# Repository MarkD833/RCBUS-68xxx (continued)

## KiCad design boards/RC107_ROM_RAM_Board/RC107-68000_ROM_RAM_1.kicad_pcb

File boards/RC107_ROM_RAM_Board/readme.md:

# ROM & RAM board - V2 - 1M ROM + 1M RAM

# Details
The ROM & RAM board is designed to plug into an RCBus-80 backplane with support for 1M ROM (via 2x SST39SF040 FLASH chips) and 1M RAM (via 2x Alliance Memory AS6C4008 SRAMs). The FLASH chips and SRAMs are used as a pair to allow 16-bit wide memory accesses.

## Address Decoding
The address decoding is carried out by a 74LS138 and divides the lower 8Mb of memory space into eight 1Mb blocks. Each pair of chips can be assigned to any of the 8 chip selects - but not both pairs to the same chip select.

**Note:** If this is the only memory board in the 68000 system, then a pair of FLASH chips should be assigned to /CS0 so that the 68000 finds the stack pointer and program counter on boot.

**Note:** If this board is used with an MC68302 processor, then see the note further down regarding the ability to remap the ROM & RAM devices.

## Bus Width 
A 74LS139 generates the read and write signals for each of the memory chips and takes care of byte or word accesses.

## DTACK
A 74LS125 is used to generate a simple /DTACK signal driven directly from the EEPROM and SRAM chip select signals without any wait period.

# Board Assembly
Assembly of the board should be fairly straightforward as there are no surface mount devices to deal with.

Note the location of the decoupling capacitors for the memory devices are located within the IC sockets. THese decoupling capacitors should be bent over so that they do not interfere with the insertion of the memory chips.
 
When fitting the 80-pin right angle connector, initially only solder a couple of pins at opposite ends of the connector so that you can make any adjustments if the board is not vertical when fitted to the backplane.

Do not mix ROM & RAM chips in the same bank.

# Memory Bank Configuration
The pinout of the 32-pin FLASH and SRAM chips are slightly different and in order to accommodate both types, a pair of jumpers need to be set per chip. J6,J7,J8 & J9 set the memory type fitted to memory bank #0 and J2,J3,J4 & J5 set the memory type fitted to memory bank #1.

# Jumpers
+ FLASH ROM chips installed in Bank #1
  + J2: Jumper pins 1-2
  + J3: Jumper pins 2-3
  + J4: Jumper pins 1-2
  + J5: Jumper pins 2-3
+ RAM chips installed in Bank #1
  + J2: Jumper pins 2-3
  + J3: Jumper pins 1-2
  + J4: Jumper pins 2-3
  + J5: Jumper pins 1-2
+ FLASH ROM chips installed in Bank #0
  + J6: Jumper pins 2-3
  + J7: Jumper pins 1-2
  + J8: Jumper pins 2-3
  + J9: Jumper pins 1-2
+ RAM chips installed in Bank #0
  + J6: Jumper pins 1-2
  + J7: Jumper pins 2-3
  + J8: Jumper pins 1-2
  + J9: Jumper pins 2-3
+ J10: Memory Address selection
  + $000000 .. $0FFFFF
  + $100000 .. $1FFFFF
  + $200000 .. $2FFFFF
  + $300000 .. $3FFFFF
  + $400000 .. $4FFFFF
  + $500000 .. $5FFFFF
+ J11 (with J10): Specify the memory address for bank #0
+ J12 (with J10): Specify the memory address for bank #1
+ JP1: Solder link to connect RCBus /CS_ROM to /CS_BANK0 (Bank 0 must have FLASH memory fitted).
+ JP2: Solder link to connect RCBus /CS_RAM to /CS_BANK1 (Bank 1 must have SRAM memory fitted).

# MC68302 ROM & RAM Remapping

If the version of the MC68302 monitor is used that makes use of remapping the chip select signals, then the following hardware changes are required to this board:
  + U1 (74LS125) should be removed as the 68302 is configured to generate the /DTACK signals for /CS0 and /CS1 itself
  + U5 (74LS138) should be removed as the 68302 is configured to generate the chip select signals itself
  + Solder links JP1 and JP2 on the rear of the board must be made.
  
# Errors
Nothing yet - but give it time :-(

# History
+ v2.0 - corrected missing /CS signals, fixed J4 & J5 pitch, added 10K pullups to /CS lines
+ v1.0 - initial designed

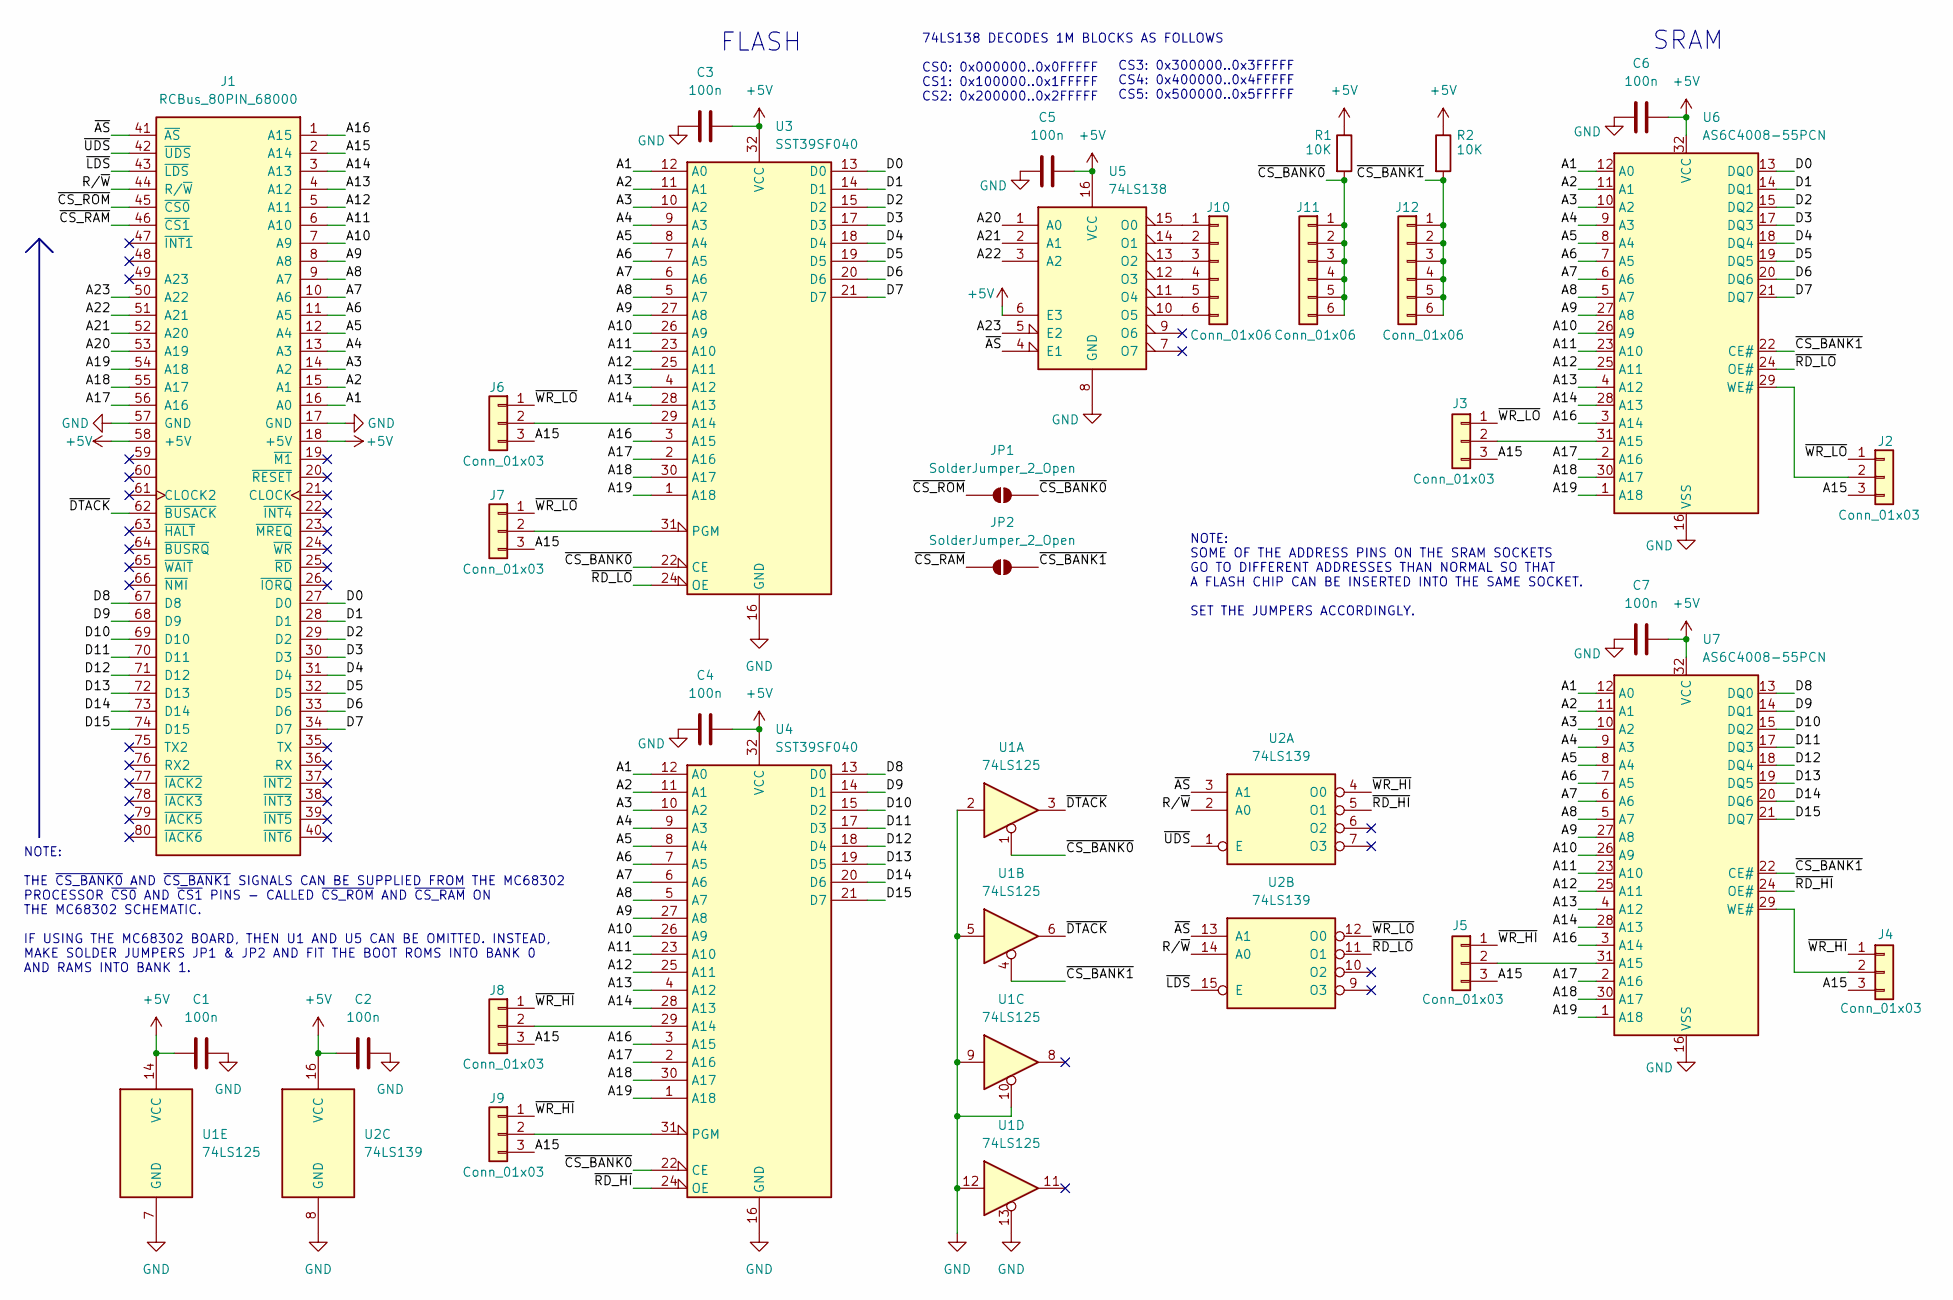
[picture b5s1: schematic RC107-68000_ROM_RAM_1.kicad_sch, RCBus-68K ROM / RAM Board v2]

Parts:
C1, C2, C3, C4, C5, C6, C7: 100n; C_Disc_D5.0mm_W2.5mm_P2.50mm
J1: RCBus_80PIN_68000; RCBus_80p_Medium
J2, J3, J4, J5, J6, J7, J8, J9: Conn_01x03; PinHeader_1x03_P2.54mm_Vertical
J10, J11, J12: Conn_01x06; PinHeader_1x06_P2.54mm_Vertical
JP1, JP2: SolderJumper_2_Open; SolderJumper-2_P1.3mm_Open_Pad1.0x1.5mm
R1, R2: 10K; R_Axial_DIN0207_L6.3mm_D2.5mm_P7.62mm_Horizontal
U1: 74LS125; DIP-14_W7.62mm
U2: 74LS139; DIP-16_W7.62mm
U3, U4: SST39SF040; DIP-32_W15.24mm
U5: 74LS138; DIP-16_W7.62mm
U6, U7: AS6C4008-55PCN; DIP-32_W15.24mm

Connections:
+5V: C1.1, C2.1, C3.2, C4.2, C5.2, C6.2, C7.2, J1.18 (+5V), J1.58 (+5V), R1.1, R2.1, U1.14 (VCC), U2.16 (VCC), U3.32 (VCC), U4.32 (VCC), U5.6 (E3), U5.16 (VCC), U6.32 (VCC), U7.32 (VCC)
/A1: J1.16 (A0), U3.12 (A0), U4.12 (A0), U6.12 (A0), U7.12 (A0)
/A2: J1.15 (A1), U3.11 (A1), U4.11 (A1), U6.11 (A1), U7.11 (A1)
/A3: J1.14 (A2), U3.10 (A2), U4.10 (A2), U6.10 (A2), U7.10 (A2)
/A4: J1.13 (A3), U3.9 (A3), U4.9 (A3), U6.9 (A3), U7.9 (A3)
/A5: J1.12 (A4), U3.8 (A4), U4.8 (A4), U6.8 (A4), U7.8 (A4)
/A6: J1.11 (A5), U3.7 (A5), U4.7 (A5), U6.7 (A5), U7.7 (A5)
/A7: J1.10 (A6), U3.6 (A6), U4.6 (A6), U6.6 (A6), U7.6 (A6)
/A8: J1.9 (A7), U3.5 (A7), U4.5 (A7), U6.5 (A7), U7.5 (A7)
/A9: J1.8 (A8), U3.27 (A8), U4.27 (A8), U6.27 (A8), U7.27 (A8)
/A10: J1.7 (A9), U3.26 (A9), U4.26 (A9), U6.26 (A9), U7.26 (A9)
/A11: J1.6 (A10), U3.23 (A10), U4.23 (A10), U6.23 (A10), U7.23 (A10)
/A12: J1.5 (A11), U3.25 (A11), U4.25 (A11), U6.25 (A11), U7.25 (A11)
/A13: J1.4 (A12), U3.4 (A12), U4.4 (A12), U6.4 (A12), U7.4 (A12)
/A14: J1.3 (A13), U3.28 (A13), U4.28 (A13), U6.28 (A13), U7.28 (A13)
/A15: J1.2 (A14), J2.3, J3.3, J4.3, J5.3, J6.3, J7.3, J8.3, J9.3
/A16: J1.1 (A15), U3.3 (A15), U4.3 (A15), U6.3 (A14), U7.3 (A14)
/A17: J1.56 (A16), U3.2 (A16), U4.2 (A16), U6.2 (A16), U7.2 (A16)
/A18: J1.55 (A17), U3.30 (A17), U4.30 (A17), U6.30 (A17), U7.30 (A17)
/A19: J1.54 (A18), U3.1 (A18), U4.1 (A18), U6.1 (A18), U7.1 (A18)
/A20: J1.53 (A19), U5.1 (A0)
/A21: J1.52 (A20), U5.2 (A1)
/A22: J1.51 (A21), U5.3 (A2)
/A23: J1.50 (A22), U5.5 (E2)
/D0: J1.27 (D0), U3.13 (D0), U6.13 (DQ0)
/D1: J1.28 (D1), U3.14 (D1), U6.14 (DQ1)
/D2: J1.29 (D2), U3.15 (D2), U6.15 (DQ2)
/D3: J1.30 (D3), U3.17 (D3), U6.17 (DQ3)
/D4: J1.31 (D4), U3.18 (D4), U6.18 (DQ4)
/D5: J1.32 (D5), U3.19 (D5), U6.19 (DQ5)
/D6: J1.33 (D6), U3.20 (D6), U6.20 (DQ6)
/D7: J1.34 (D7), U3.21 (D7), U6.21 (DQ7)
/D8: J1.67 (D8), U4.13 (D0), U7.13 (DQ0)
/D9: J1.68 (D9), U4.14 (D1), U7.14 (DQ1)
/D10: J1.69 (D10), U4.15 (D2), U7.15 (DQ2)
/D11: J1.70 (D11), U4.17 (D3), U7.17 (DQ3)
/D12: J1.71 (D12), U4.18 (D4), U7.18 (DQ4)
/D13: J1.72 (D13), U4.19 (D5), U7.19 (DQ5)
/D14: J1.73 (D14), U4.20 (D6), U7.20 (DQ6)
/D15: J1.74 (D15), U4.21 (D7), U7.21 (DQ7)
/R/~W: J1.44 (R/~W), U2.2 (A0), U2.14 (A0)
/~AS: J1.41 (~AS), U2.3 (A1), U2.13 (A1), U5.4 (E1)
/~CS_BANK0: J11.1, J11.2, J11.3, J11.4, J11.5, J11.6, JP1.2 (B), R1.2, U1.1, U3.22 (CE), U4.22 (CE)
/~CS_BANK1: J12.1, J12.2, J12.3, J12.4, J12.5, J12.6, JP2.2 (B), R2.2, U1.4, U6.22 (CE#), U7.22 (CE#)
/~CS_RAM: J1.46 (~CS1), JP2.1 (A)
/~CS_ROM: J1.45 (~CS0), JP1.1 (A)
/~DTACK: J1.62 (~BUSACK), U1.3, U1.6
/~LDS: J1.43 (~LDS), U2.15 (E)
/~RD_HI: U2.5 (O1), U4.24 (OE), U7.24 (OE#)
/~RD_LO: U2.11 (O1), U3.24 (OE), U6.24 (OE#)
/~UDS: J1.42 (~UDS), U2.1 (E)
/~WR_HI: J4.1, J5.1, J8.1, J9.1, U2.4 (O0)
/~WR_LO: J2.1, J3.1, J6.1, J7.1, U2.12 (O0)
GND: C1.2, C2.2, C3.1, C4.1, C5.1, C6.1, C7.1, J1.17 (GND), J1.57 (GND), U1.2, U1.5, U1.7 (GND), U1.9, U1.10, U1.12, U1.13, U2.8 (GND), U3.16 (GND), U4.16 (GND), U5.8 (GND), U6.16 (VSS), U7.16 (VSS)
unnamed: J2.2, U6.29 (WE#)
unnamed: J3.2, U6.31 (A15)
unnamed: J4.2, U7.29 (WE#)
unnamed: J5.2, U7.31 (A15)
unnamed: J6.2, U3.29 (A14)
unnamed: J7.2, U3.31 (PGM)
unnamed: J8.2, U4.29 (A14)
unnamed: J9.2, U4.31 (PGM)
unnamed: J10.1, U5.15 (O0)
unnamed: J10.2, U5.14 (O1)
unnamed: J10.3, U5.13 (O2)
unnamed: J10.4, U5.12 (O3)
unnamed: J10.5, U5.11 (O4)
unnamed: J10.6, U5.10 (O5)

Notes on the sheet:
CS3: 0x300000..0x3FFFFF CS4: 0x400000..0x4FFFFF CS5: 0x500000..0x5FFFFF
FLASH
NOTE: THE ~{CS_BANK0} AND ~{CS_BANK1} SIGNALS CAN BE SUPPLIED FROM THE MC68302 PROCESSOR ~{CS0} AND ~{CS1} PINS - CALLED ~{CS_ROM} AND ~{CS_RAM} ON THE MC68302 SCHEMATIC. IF USING THE MC68302 BOARD, THEN U1 AND U5 CAN BE OMITTED. INSTEAD, MAKE SOLDER JUMPERS JP1 & JP2 AND FIT THE BOOT ROMS INTO BAN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
74LS138 DECODES 1M BLOCKS AS FOLLOWS CS0: 0x000000..0x0FFFFF CS1: 0x100000..0x1FFFFF CS2: 0x200000..0x2FFFFF
NOTE: SOME OF THE ADDRESS PINS ON THE SRAM SOCKETS GO TO DIFFERENT ADDRESSES THAN NORMAL SO THAT A FLASH CHIP CAN BE INSERTED INTO THE SAME SOCKET. SET THE JUMPERS ACCORDINGLY.
SRAM

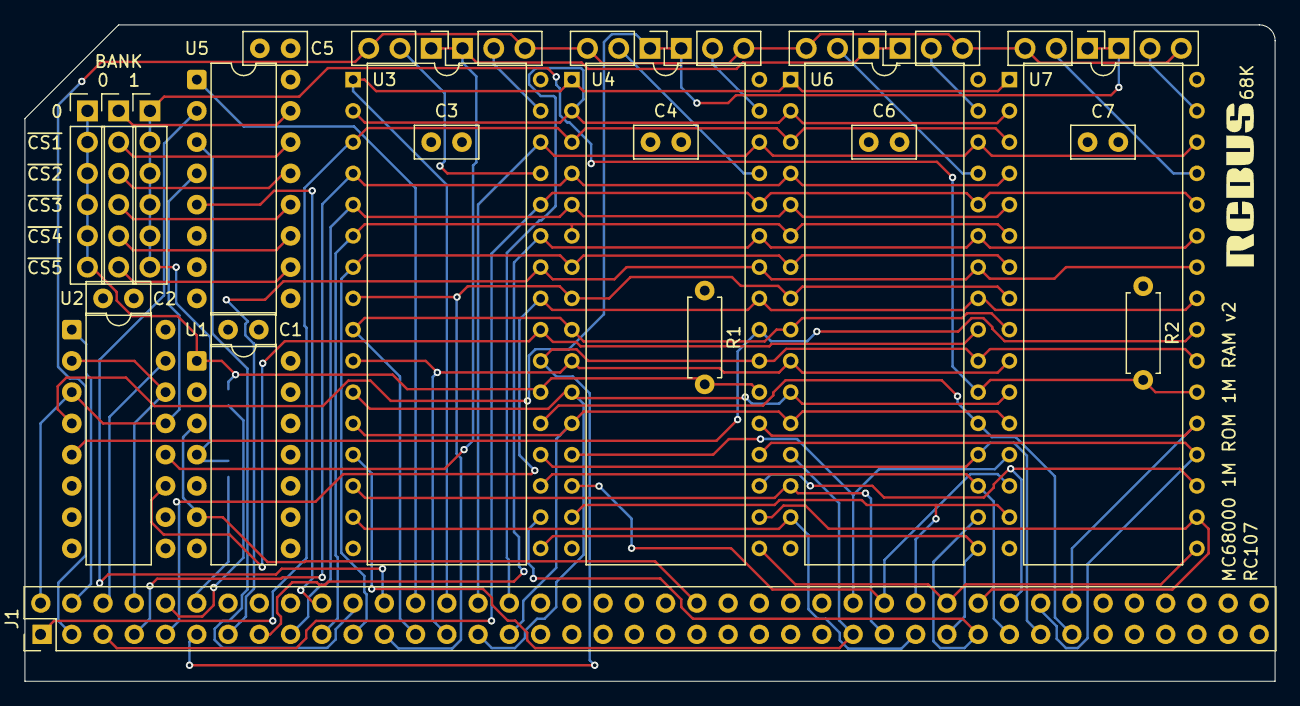
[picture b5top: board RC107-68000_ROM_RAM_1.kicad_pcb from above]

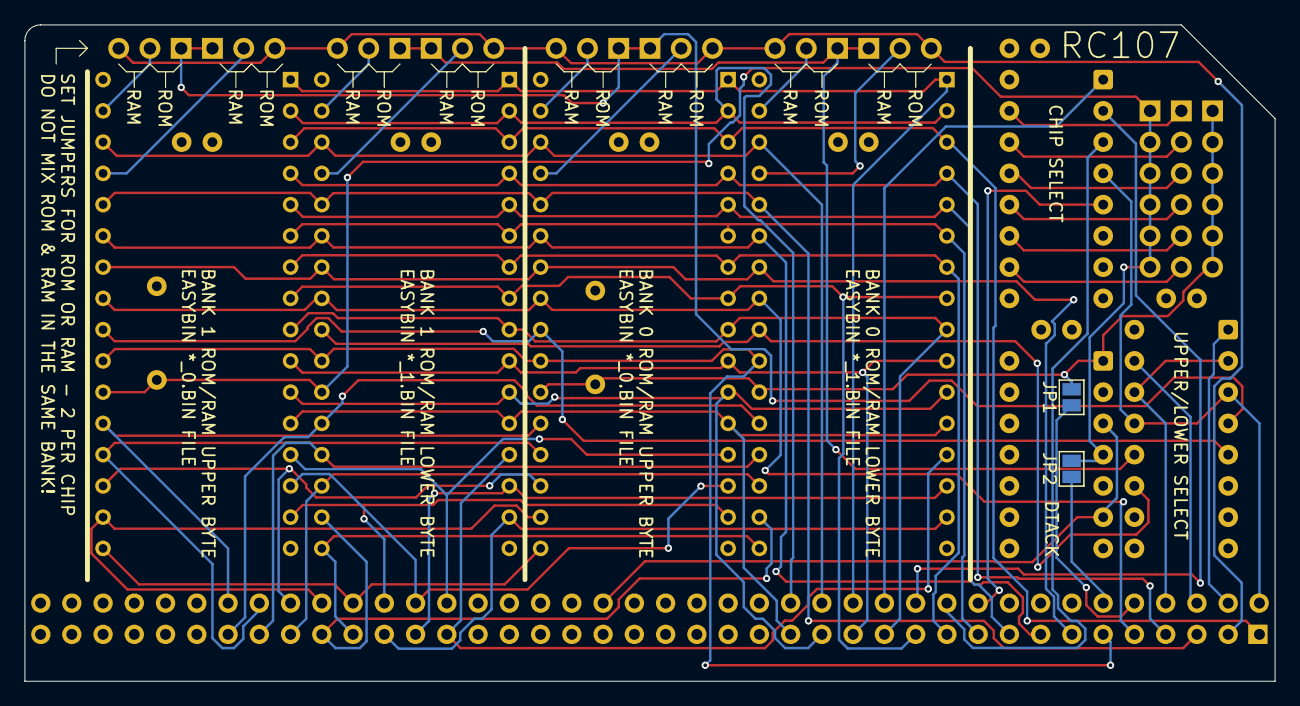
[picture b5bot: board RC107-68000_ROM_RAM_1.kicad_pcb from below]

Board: 4 copper layers, 101.6 x 53.3 mm, 30 parts (2 on the bottom side), 68 nets.

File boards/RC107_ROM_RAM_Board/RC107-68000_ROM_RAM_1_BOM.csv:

"Reference","Value","Qty","Description"
"C1,C2,C3,C4,C5,C6,C7","100n","7","Unpolarized ceramic capacitor"
"J1","RCBus_80PIN_68000","1","Generic connector, double row, 02x40, right angle"
"J2,J3,J4,J5,J6,J7,J8,J9","Conn_01x03","8","Generic connector, single row, 01x03"
"J10,J11,J12","Conn_01x06","3","Generic connector, single row, 01x06"
"R1,R2","10K","2","Resistor"
"U1","74LS125","1","Quad buffer 3-State outputs"
"U2","74LS139","1","Dual Decoder 1 of 4, Active low outputs"
"U3,U4","SST39SF040","2","Silicon Storage Technology (SSF) 512k x 8 Flash ROM"
"U5","74LS138","1","Decoder 3 to 8 active low outputs"
"U6,U7","AS6C4008-55PCN","2","512K x 8 Low Power CMOS RAM, DIP-32"

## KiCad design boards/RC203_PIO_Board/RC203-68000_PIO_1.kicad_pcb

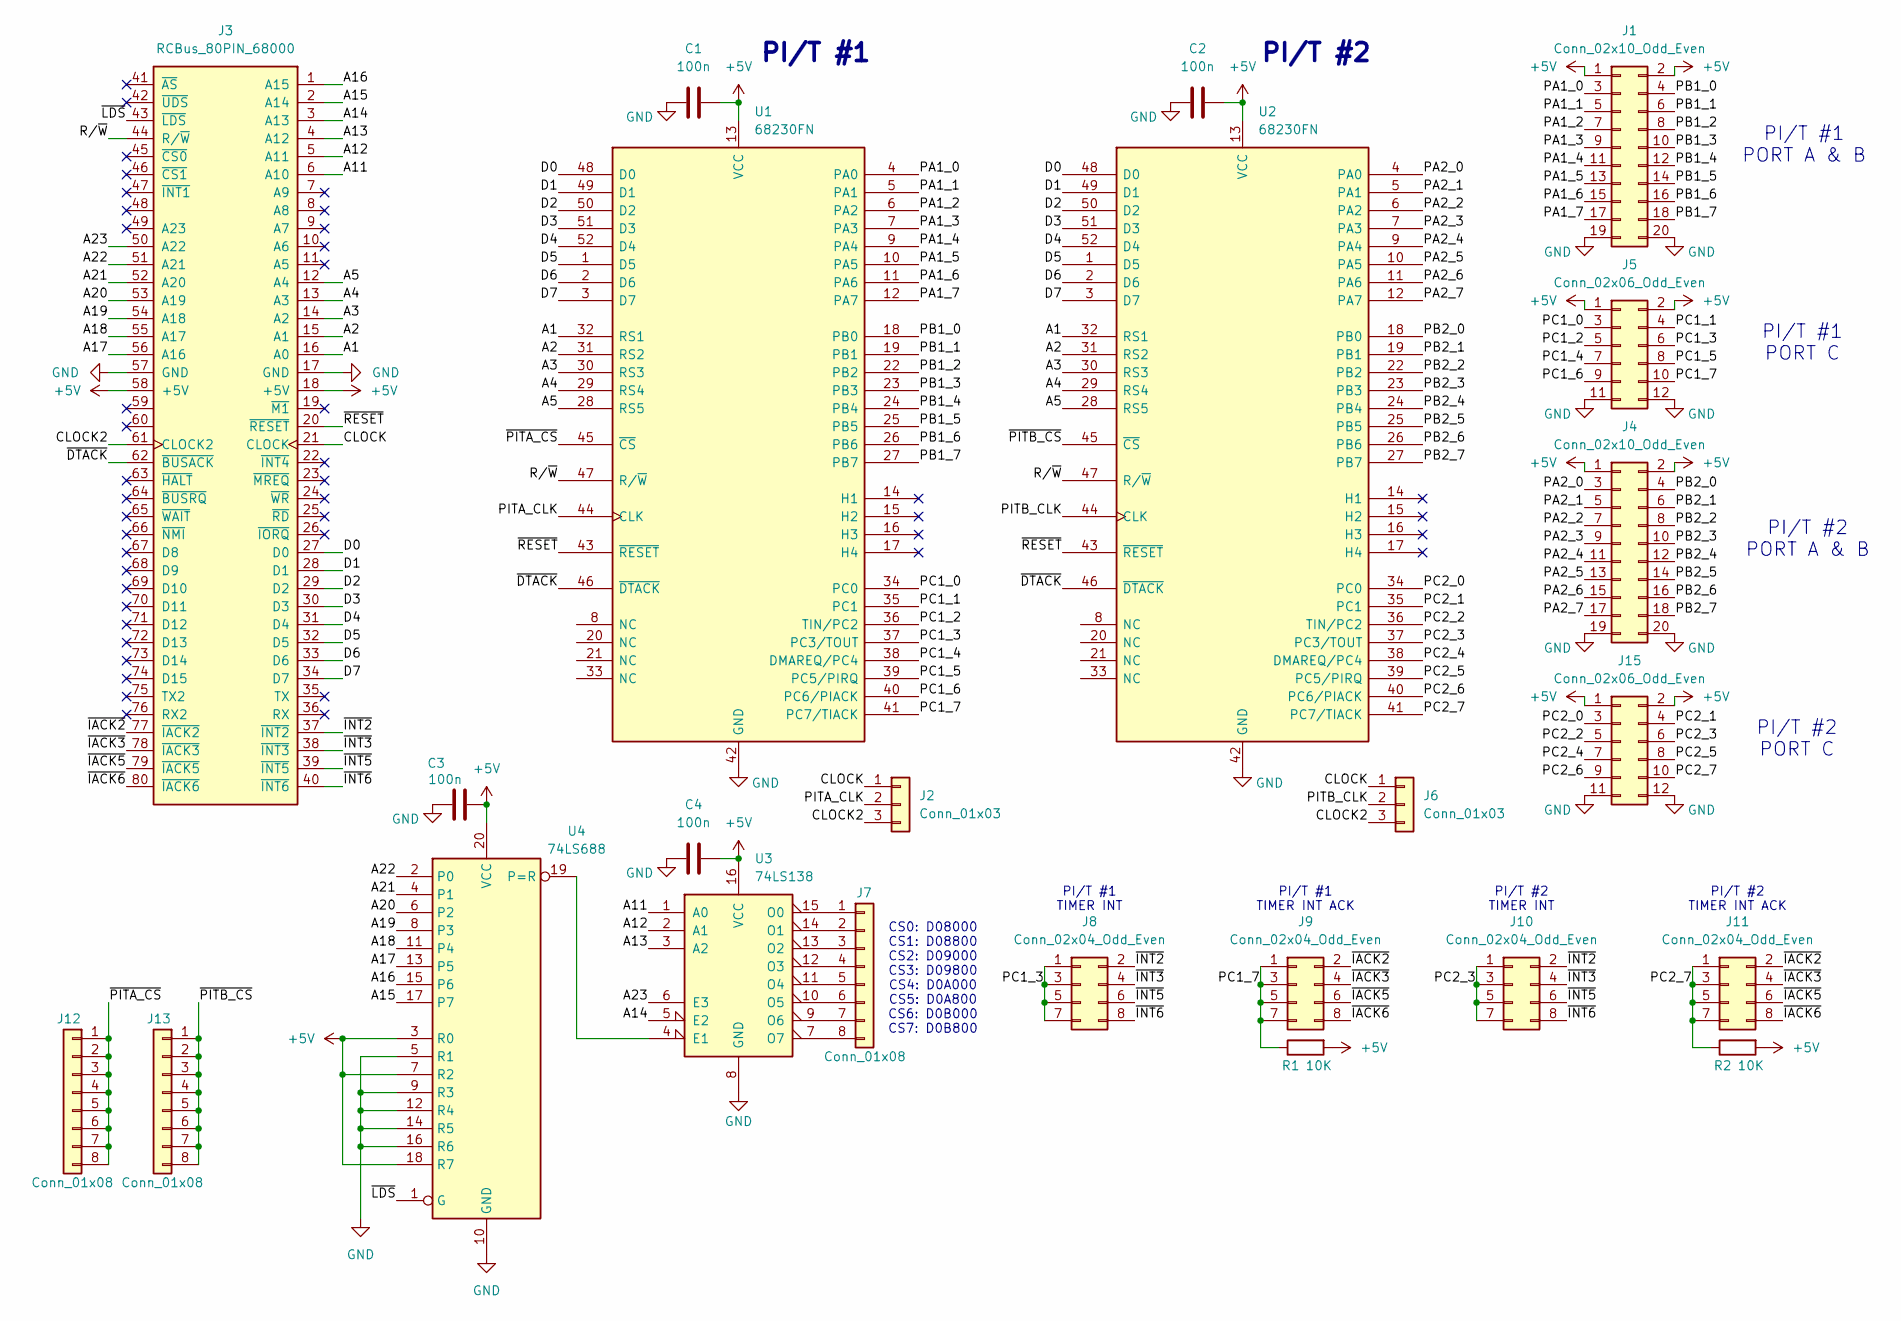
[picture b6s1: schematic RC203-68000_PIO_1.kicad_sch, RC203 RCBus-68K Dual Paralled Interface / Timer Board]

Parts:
C1, C2, C3, C4: 100n; C_Disc_D5.0mm_W2.5mm_P2.50mm
J1, J4: Conn_02x10_Odd_Even; PinHeader_2x10_P2.54mm_Horizontal
J2, J6: Conn_01x03; PinHeader_1x03_P2.54mm_Vertical
J3: RCBus_80PIN_68000; RCBus_80p_Medium
J5, J15: Conn_02x06_Odd_Even; PinHeader_2x06_P2.54mm_Horizontal
J7, J12, J13: Conn_01x08; PinHeader_1x08_P2.54mm_Vertical
J8, J9, J10, J11: Conn_02x04_Odd_Even; PinHeader_2x04_P2.54mm_Vertical
R1, R2: 10K; R_Axial_DIN0207_L6.3mm_D2.5mm_P7.62mm_Horizontal
U1, U2: 68230FN; PLCC-52_THT-Socket
U3: 74LS138; DIP-16_W7.62mm
U4: 74LS688; DIP-20_W7.62mm

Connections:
+5V: C1.1, C2.1, C3.2, C4.2, J1.1, J1.2, J3.18 (+5V), J3.58 (+5V), J4.1, J4.2, J5.1, J5.2, J15.1, J15.2, R1.2, R2.2, U1.13 (VCC), U2.13 (VCC), U3.16 (VCC), U4.3 (R0), U4.7 (R2), U4.18 (R7), U4.20 (VCC)
/A1: J3.16 (A0), U1.32 (RS1), U2.32 (RS1)
/A2: J3.15 (A1), U1.31 (RS2), U2.31 (RS2)
/A3: J3.14 (A2), U1.30 (RS3), U2.30 (RS3)
/A4: J3.13 (A3), U1.29 (RS4), U2.29 (RS4)
/A5: J3.12 (A4), U1.28 (RS5), U2.28 (RS5)
/A11: J3.6 (A10), U3.1 (A0)
/A12: J3.5 (A11), U3.2 (A1)
/A13: J3.4 (A12), U3.3 (A2)
/A14: J3.3 (A13), U3.5 (E2)
/A15: J3.2 (A14), U4.17 (P7)
/A16: J3.1 (A15), U4.15 (P6)
/A17: J3.56 (A16), U4.13 (P5)
/A18: J3.55 (A17), U4.11 (P4)
/A19: J3.54 (A18), U4.8 (P3)
/A20: J3.53 (A19), U4.6 (P2)
/A21: J3.52 (A20), U4.4 (P1)
/A22: J3.51 (A21), U4.2 (P0)
/A23: J3.50 (A22), U3.6 (E3)
/CLOCK: J2.1, J3.21 (CLOCK), J6.1
/CLOCK2: J2.3, J3.61 (CLOCK2), J6.3
/D0: J3.27 (D0), U1.48 (D0), U2.48 (D0)
/D1: J3.28 (D1), U1.49 (D1), U2.49 (D1)
/D2: J3.29 (D2), U1.50 (D2), U2.50 (D2)
/D3: J3.30 (D3), U1.51 (D3), U2.51 (D3)
/D4: J3.31 (D4), U1.52 (D4), U2.52 (D4)
/D5: J3.32 (D5), U1.1 (D5), U2.1 (D5)
/D6: J3.33 (D6), U1.2 (D6), U2.2 (D6)
/D7: J3.34 (D7), U1.3 (D7), U2.3 (D7)
/PA1_0: J1.3, U1.4 (PA0)
/PA1_1: J1.5, U1.5 (PA1)
/PA1_2: J1.7, U1.6 (PA2)
/PA1_3: J1.9, U1.7 (PA3)
/PA1_4: J1.11, U1.9 (PA4)
/PA1_5: J1.13, U1.10 (PA5)
/PA1_6: J1.15, U1.11 (PA6)
/PA1_7: J1.17, U1.12 (PA7)
/PA2_0: J4.3, U2.4 (PA0)
/PA2_1: J4.5, U2.5 (PA1)
/PA2_2: J4.7, U2.6 (PA2)
/PA2_3: J4.9, U2.7 (PA3)
/PA2_4: J4.11, U2.9 (PA4)
/PA2_5: J4.13, U2.10 (PA5)
/PA2_6: J4.15, U2.11 (PA6)
/PA2_7: J4.17, U2.12 (PA7)
/PB1_0: J1.4, U1.18 (PB0)
/PB1_1: J1.6, U1.19 (PB1)
/PB1_2: J1.8, U1.22 (PB2)
/PB1_3: J1.10, U1.23 (PB3)
/PB1_4: J1.12, U1.24 (PB4)
/PB1_5: J1.14, U1.25 (PB5)
/PB1_6: J1.16, U1.26 (PB6)
/PB1_7: J1.18, U1.27 (PB7)
/PB2_0: J4.4, U2.18 (PB0)
/PB2_1: J4.6, U2.19 (PB1)
/PB2_2: J4.8, U2.22 (PB2)
/PB2_3: J4.10, U2.23 (PB3)
/PB2_4: J4.12, U2.24 (PB4)
/PB2_5: J4.14, U2.25 (PB5)
/PB2_6: J4.16, U2.26 (PB6)
/PB2_7: J4.18, U2.27 (PB7)
/PC1_0: J5.3, U1.34 (PC0)
/PC1_1: J5.4, U1.35 (PC1)
/PC1_2: J5.5, U1.36 (TIN/PC2)
/PC1_3: J5.6, J8.1, J8.3, J8.5, J8.7, U1.37 (PC3/TOUT)
/PC1_4: J5.7, U1.38 (DMAREQ/PC4)
/PC1_5: J5.8, U1.39 (PC5/PIRQ)
/PC1_6: J5.9, U1.40 (PC6/PIACK)
/PC1_7: J5.10, J9.1, J9.3, J9.5, J9.7, R1.1, U1.41 (PC7/TIACK)
/PC2_0: J15.3, U2.34 (PC0)
/PC2_1: J15.4, U2.35 (PC1)
/PC2_2: J15.5, U2.36 (TIN/PC2)
/PC2_3: J10.1, J10.3, J10.5, J10.7, J15.6, U2.37 (PC3/TOUT)
/PC2_4: J15.7, U2.38 (DMAREQ/PC4)
/PC2_5: J15.8, U2.39 (PC5/PIRQ)
/PC2_6: J15.9, U2.40 (PC6/PIACK)
/PC2_7: J11.1, J11.3, J11.5, J11.7, J15.10, R2.1, U2.41 (PC7/TIACK)
/PITA_CLK: J2.2, U1.44 (CLK)
/PITB_CLK: J6.2, U2.44 (CLK)
/R/~W: J3.44 (R/~W), U1.47 (R/~W), U2.47 (R/~W)
/~DTACK: J3.62 (~BUSACK), U1.46 (~DTACK), U2.46 (~DTACK)
/~IACK2: J3.77 (~IACK2), J9.2, J11.2
/~IACK3: J3.78 (~IACK3), J9.4, J11.4
/~IACK5: J3.79 (~IACK5), J9.6, J11.6
/~IACK6: J3.80 (~IACK6), J9.8, J11.8
/~INT2: J3.37 (~INT2), J8.2, J10.2
/~INT3: J3.38 (~INT3), J8.4, J10.4
/~INT5: J3.39 (~INT5), J8.6, J10.6
/~INT6: J3.40 (~INT6), J8.8, J10.8
/~LDS: J3.43 (~LDS), U4.1 (G)
/~PITA_CS: J12.1, J12.2, J12.3, J12.4, J12.5, J12.6, J12.7, J12.8, U1.45 (~CS)
/~PITB_CS: J13.1, J13.2, J13.3, J13.4, J13.5, J13.6, J13.7, J13.8, U2.45 (~CS)
/~RESET: J3.20 (~RESET), U1.43 (~RESET), U2.43 (~RESET)
GND: C1.2, C2.2, C3.1, C4.1, J1.19, J1.20, J3.17 (GND), J3.57 (GND), J4.19, J4.20, J5.11, J5.12, J15.11, J15.12, U1.42 (GND), U2.42 (GND), U3.8 (GND), U4.5 (R1), U4.9 (R3), U4.10 (GND), U4.12 (R4), U4.14 (R5), U4.16 (R6)
unnamed: J7.1, U3.15 (O0)
unnamed: J7.2, U3.14 (O1)
unnamed: J7.3, U3.13 (O2)
unnamed: J7.4, U3.12 (O3)
unnamed: J7.5, U3.11 (O4)
unnamed: J7.6, U3.10 (O5)
unnamed: J7.7, U3.9 (O6)
unnamed: J7.8, U3.7 (O7)
unnamed: U3.4 (E1), U4.19 (P=R)

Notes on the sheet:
PI/T #2 TIMER INT ACK
PI/T #1 TIMER INT ACK
PI/T #2
CS0: D08000 CS1: D08800 CS2: D09000 CS3: D09800 CS4: D0A000 CS5: D0A800 CS6: D0B000 CS7: D0B800
PI/T #1 PORT C
PI/T #1 TIMER INT
PI/T #2 TIMER INT
PI/T #2 PORT A & B
PI/T #2 PORT C
PI/T #1
PI/T #1 PORT A & B

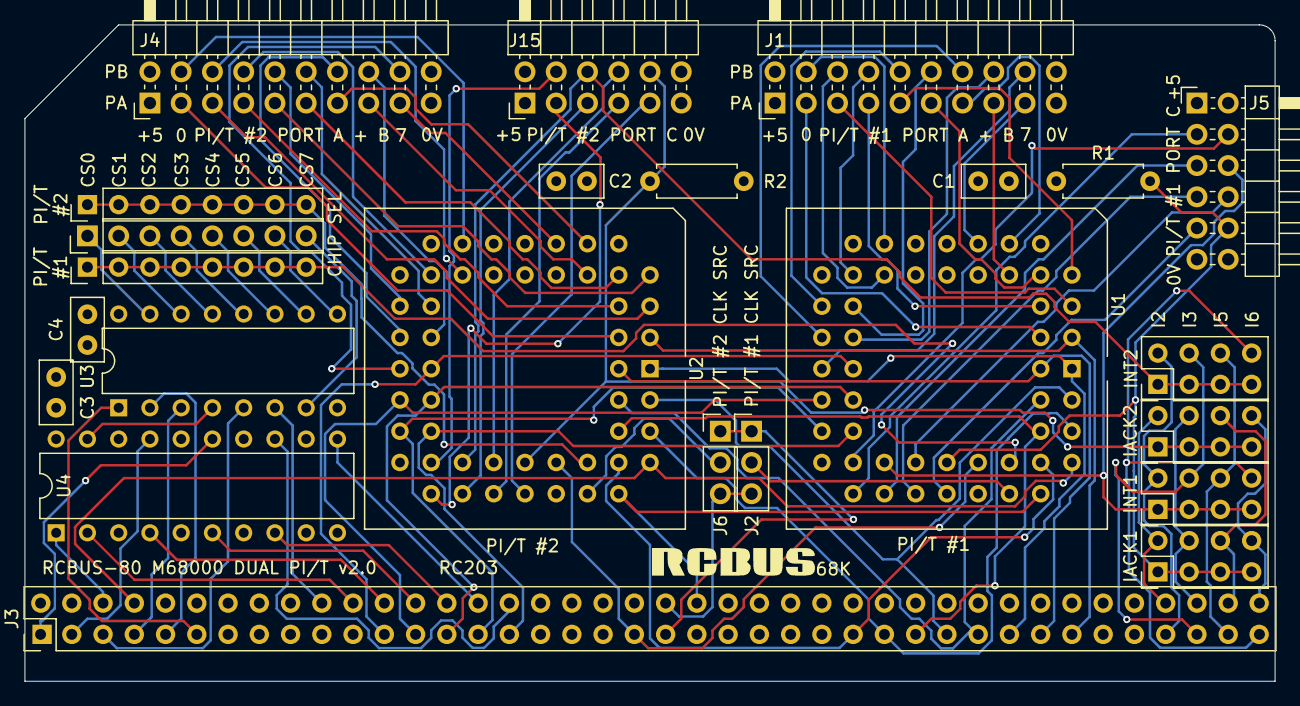
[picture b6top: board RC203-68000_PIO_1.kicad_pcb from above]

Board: 4 copper layers, 101.6 x 53.3 mm, 24 parts (0 on the bottom side), 103 nets.

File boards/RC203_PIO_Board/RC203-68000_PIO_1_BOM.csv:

Reference,Value,Footprint,Qty,Description
"C1,C2,C3,C4",100n,Capacitor_THT:C_Disc_D5.0mm_W2.5mm_P2.50mm,4,Unpolarized ceramic capacitor
"J1,J4,J5",Conn_02x08_Odd_Even,MyLibrary2023:PinHeader_2x08_P2.54mm_Vertical,3,"Generic connector, double row, 02x08, right angle"
"J2,J6",Conn_01x03,Connector_PinHeader_2.54mm:PinHeader_1x03_P2.54mm_Vertical,2,"Generic connector, single row, 01x03"
J3,RCBus_80PIN_68000,MyLibrary2023:RCBus_80p_Medium,1,"Generic connector, double row, 02x40, right angle"
"J7,J12,J13",Conn_01x08,Connector_PinHeader_2.54mm:PinHeader_1x08_P2.54mm_Vertical,3,"Generic connector, single row, 01x08"
"J8,J9,J10,J11",Conn_02x04_Odd_Even,MyLibrary2023:PinHeader_2x04_P2.54mm_Vertical,4,"Generic connector, double row, 02x04"
J14,Conn_02x03_Odd_Even,Connector_PinSocket_2.54mm:PinSocket_2x03_P2.54mm_Vertical,1,"Generic connector, double row, 02x03, right angle"
J15,Conn_01x06,Connector_PinSocket_2.54mm:PinSocket_1x06_P2.54mm_Vertical,1,"Generic connector, single row, 01x06, right angle"
"U1,U2",MC68230,MyLibrary2023:DIP-48_W15.24mm_Socket,2,Parallel Interface / Timer
U3,74LS138,Package_DIP:DIP-16_W7.62mm_Socket,1,Decoder 3 to 8 active low outputs
U4,74LS688,MyLibrary2023:DIP-20_W7.62mm_Socket,1,8-bit magnitude comparator

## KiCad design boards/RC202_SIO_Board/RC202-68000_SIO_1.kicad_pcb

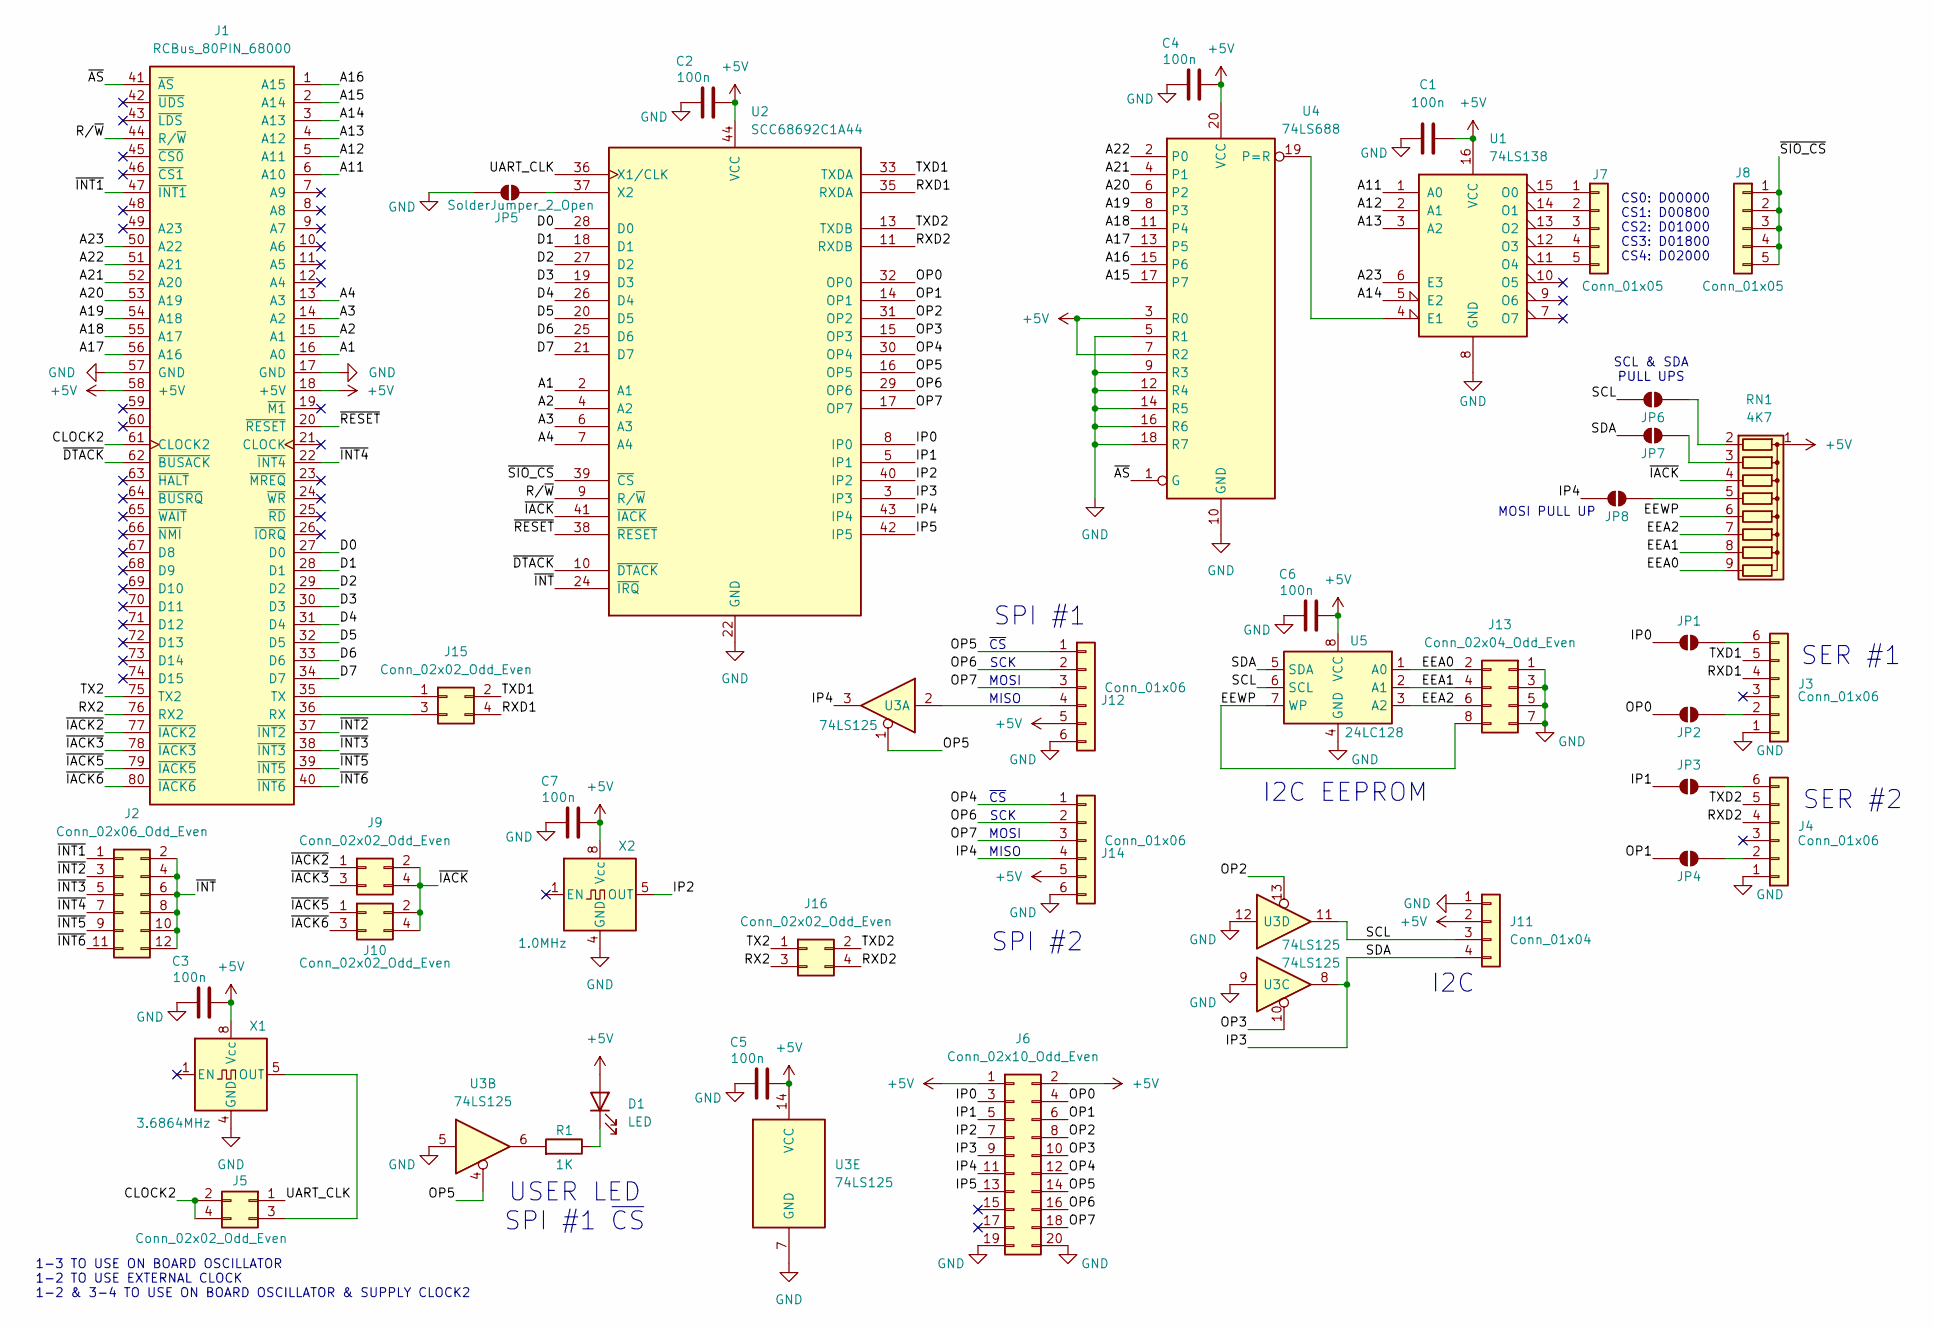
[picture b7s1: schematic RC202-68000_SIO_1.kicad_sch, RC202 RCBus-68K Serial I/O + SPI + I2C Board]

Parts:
C1, C2, C3, C4, C5, C6, C7: 100n; C_Disc_D5.0mm_W2.5mm_P2.50mm
D1: LED; LED_D3.0mm
J1: RCBus_80PIN_68000; RCBus_80p_Medium
J2: Conn_02x06_Odd_Even; PinHeader_2x06_P2.54mm_Vertical
J3, J4, J12, J14: Conn_01x06; PinSocket_1x06_P2.54mm_Horizontal
J5, J9, J10, J15, J16: Conn_02x02_Odd_Even; PinHeader_2x02_P2.54mm_Vertical
J6: Conn_02x10_Odd_Even; PinHeader_2x10_P2.54mm_Horizontal
J7, J8: Conn_01x05; PinHeader_1x05_P2.54mm_Vertical
J11: Conn_01x04; PinHeader_1x04_P2.54mm_Horizontal
J13: Conn_02x04_Odd_Even; PinHeader_2x04_P2.54mm_Vertical
JP1, JP2, JP3, JP4, JP6, JP7, JP8: SolderJumper; SolderJumper-2_P1.3mm_Open_Pad1.0x1.5mm
JP5: SolderJumper_2_Open; SolderJumper-2_P1.3mm_Open_Pad1.0x1.5mm
R1: 1K; R_Axial_DIN0207_L6.3mm_D2.5mm_P7.62mm_Horizontal
RN1: 4K7; R_Array_SIP9
U1: 74LS138; DIP-16_W7.62mm
U2: SCC68692C1A44; PLCC-44_THT-Socket
U3: 74LS125; DIP-14_W7.62mm
U4: 74LS688; DIP-20_W7.62mm
U5: 24LC128; DIP-8_W7.62mm
X1: 3.6864MHz; Oscillator_DIP-8
X2: 1.0MHz; Oscillator_DIP-8

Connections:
+5V: C1.2, C2.2, C3.2, C4.2, C5.2, C6.2, C7.2, D1.2 (A), J1.18 (+5V), J1.58 (+5V), J6.1, J6.2, J11.2, J12.5, J14.5, RN1.1 (common), U1.16 (VCC), U2.44 (VCC), U3.14 (VCC), U4.3 (R0), U4.7 (R2), U4.20 (VCC), U5.8 (VCC), X1.8 (Vcc), X2.8 (Vcc)
/A1: J1.16 (A0), U2.2 (A1)
/A2: J1.15 (A1), U2.4 (A2)
/A3: J1.14 (A2), U2.6 (A3)
/A4: J1.13 (A3), U2.7 (A4)
/A11: J1.6 (A10), U1.1 (A0)
/A12: J1.5 (A11), U1.2 (A1)
/A13: J1.4 (A12), U1.3 (A2)
/A14: J1.3 (A13), U1.5 (E2)
/A15: J1.2 (A14), U4.17 (P7)
/A16: J1.1 (A15), U4.15 (P6)
/A17: J1.56 (A16), U4.13 (P5)
/A18: J1.55 (A17), U4.11 (P4)
/A19: J1.54 (A18), U4.8 (P3)
/A20: J1.53 (A19), U4.6 (P2)
/A21: J1.52 (A20), U4.4 (P1)
/A22: J1.51 (A21), U4.2 (P0)
/A23: J1.50 (A22), U1.6 (E3)
/CLOCK2: J1.61 (CLOCK2), J5.2, J5.4
/D0: J1.27 (D0), U2.28 (D0)
/D1: J1.28 (D1), U2.18 (D1)
/D2: J1.29 (D2), U2.27 (D2)
/D3: J1.30 (D3), U2.19 (D3)
/D4: J1.31 (D4), U2.26 (D4)
/D5: J1.32 (D5), U2.20 (D5)
/D6: J1.33 (D6), U2.25 (D6)
/D7: J1.34 (D7), U2.21 (D7)
/EEA0: J13.2, RN1.9 (R8), U5.1 (A0)
/EEA1: J13.4, RN1.8 (R7), U5.2 (A1)
/EEA2: J13.6, RN1.7 (R6), U5.3 (A2)
/EEWP: J13.8, RN1.6 (R5), U5.7 (WP)
/IP0: J6.3, JP1.1 (A), U2.8 (IP0)
/IP1: J6.5, JP3.1 (A), U2.5 (IP1)
/IP2: J6.7, U2.40 (IP2), X2.5 (OUT)
/IP3: J6.9, J11.4, JP7.1 (A), U2.3 (IP3), U3.8, U5.5 (SDA)
/IP4: J6.11, J14.4, JP8.1 (A), U2.43 (IP4), U3.3
/IP5: J6.13, U2.42 (IP5)
/OP0: J6.4, JP2.1 (A), U2.32 (OP0)
/OP1: J6.6, JP4.1 (A), U2.14 (OP1)
/OP2: J6.8, U2.31 (OP2), U3.13
/OP3: J6.10, U2.15 (OP3), U3.10
/OP4: J6.12, J14.1, U2.30 (OP4)
/OP5: J6.14, J12.1, U2.16 (OP5), U3.1, U3.4
/OP6: J6.16, J12.2, J14.2, U2.29 (OP6)
/OP7: J6.18, J12.3, J14.3, U2.17 (OP7)
/RX2: J1.76 (RX2), J16.3
/RXD1: J3.4, J15.4, U2.35 (RXDA)
/RXD2: J4.4, J16.4, U2.11 (RXDB)
/R/~W: J1.44 (R/~W), U2.9 (R/~W)
/SCL: J11.3, JP6.1 (A), U3.11, U5.6 (SCL)
/TX2: J1.75 (TX2), J16.1
/TXD1: J3.5, J15.2, U2.33 (TXDA)
/TXD2: J4.5, J16.2, U2.13 (TXDB)
/UART_CLK: J5.1, U2.36 (X1/CLK)
/~AS: J1.41 (~AS), U4.1 (G)
/~DTACK: J1.62 (~BUSACK), U2.10 (~DTACK)
/~IACK2: J1.77 (~IACK2), J9.1
/~IACK3: J1.78 (~IACK3), J9.3
/~IACK5: J1.79 (~IACK5), J10.1
/~IACK6: J1.80 (~IACK6), J10.3
/~IACK: J9.2, J9.4, J10.2, J10.4, RN1.4 (R3), U2.41 (~IACK)
/~INT1: J1.47 (~INT1), J2.1
/~INT2: J1.37 (~INT2), J2.3
/~INT3: J1.38 (~INT3), J2.5
/~INT4: J1.22 (~INT4), J2.7
/~INT5: J1.39 (~INT5), J2.9
/~INT6: J1.40 (~INT6), J2.11
/~INT: J2.2, J2.4, J2.6, J2.8, J2.10, J2.12, U2.24 (~IRQ)
/~RESET: J1.20 (~RESET), U2.38 (~RESET)
/~SIO_CS: J8.1, J8.2, J8.3, J8.4, J8.5, U2.39 (~CS)
GND: C1.1, C2.1, C3.1, C4.1, C5.1, C6.1, C7.1, J1.17 (GND), J1.57 (GND), J3.1, J4.1, J6.19, J6.20, J11.1, J12.6, J13.1, J13.3, J13.5, J13.7, J14.6, JP5.2 (B), U1.8 (GND), U2.22 (GND), U3.5, U3.7 (GND), U3.9, U3.12, U4.5 (R1), U4.9 (R3), U4.10 (GND), U4.12 (R4), U4.14 (R5), U4.16 (R6), U4.18 (R7), U5.4 (GND), X1.4 (GND), X2.4 (GND)
unnamed: D1.1 (K), R1.1
unnamed: J1.36 (RX), J15.3
unnamed: J1.35 (TX), J15.1
unnamed: J3.2, JP2.2 (B)
unnamed: J3.6, JP1.2 (B)
unnamed: J4.2, JP4.2 (B)
unnamed: J4.6, JP3.2 (B)
unnamed: J5.3, X1.5 (OUT)
unnamed: J7.1, U1.15 (O0)
unnamed: J7.2, U1.14 (O1)
unnamed: J7.3, U1.13 (O2)
unnamed: J7.4, U1.12 (O3)
unnamed: J7.5, U1.11 (O4)
unnamed: J12.4, U3.2
unnamed: JP5.1 (A), U2.37 (X2)
unnamed: JP6.2 (B), RN1.2 (R1)
unnamed: JP7.2 (B), RN1.3 (R2)
unnamed: JP8.2 (B), RN1.5 (R4)
unnamed: R1.2, U3.6
unnamed: U1.4 (E1), U4.19 (P=R)

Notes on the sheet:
I2C EEPROM
SCK
SCL & SDA PULL UPS
~{CS}
MOSI PULL UP
MISO
MOSI
I2C
CS0: D00000 CS1: D00800 CS2: D01000 CS3: D01800 CS4: D02000
SER #1
SER #2
SPI #1
1-3 TO USE ON BOARD OSCILLATOR 1-2 TO USE EXTERNAL CLOCK 1-2 & 3-4 TO USE ON BOARD OSCILLATOR & SUPPLY CLOCK2
USER LED SPI #1 ~{CS}
SPI #2
